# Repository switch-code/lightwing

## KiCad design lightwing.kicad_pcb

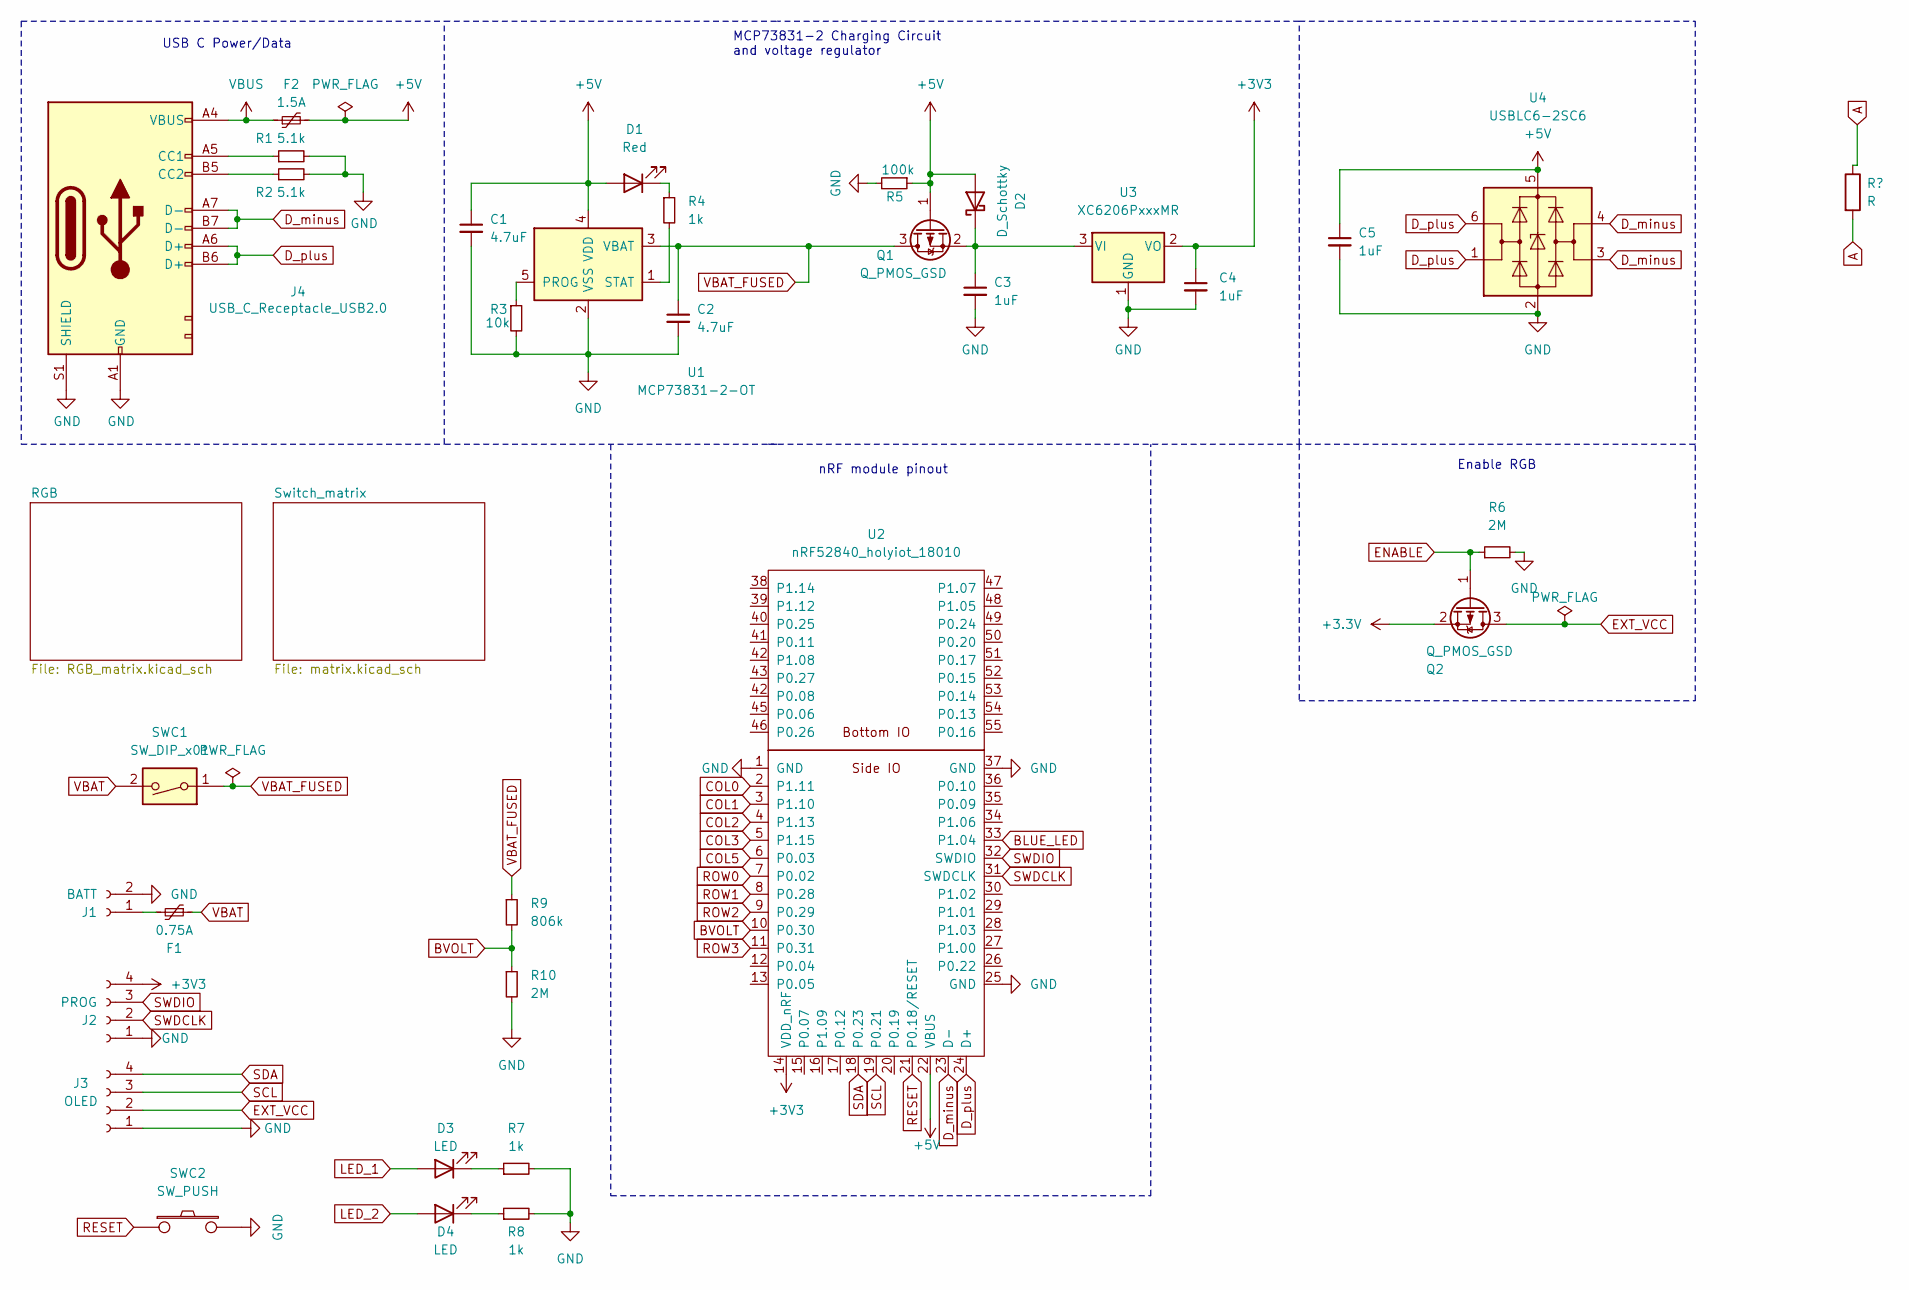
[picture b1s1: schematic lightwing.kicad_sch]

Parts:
C1, C2: 4.7uF; C-0805_2012Metric
C3, C4, C5: 1uF; C-0805_2012Metric
D1: Red; LED_0603_1608Metric_Castellated
D2: D_Schottky; D_1206_3216Metric
D3, D4: LED; LED_0603_1608Metric_Castellated
F1: 0.75A; Fuse_1206_3216Metric
F2: 1.5A; Fuse_1206_3216Metric
J1: BATT; JST_EH_B2B-EH-A_1x02_P2.50mm_Vertical
J2: PROG; PinHeader_1x04_P2.54mm_Vertical
J3: OLED; SSD1306-0.91-OLED-4pin-128x32
J4: USB_C_Receptacle_USB2.0; HRO-TYPE-C-31-M-12-HandSoldering-NoSBU
Q1, Q2: Q_PMOS_GSD; SOT-23
R1, R2: 5.1k; R-0805_2012Metric
R3: 10k; R-0805_2012Metric
R4, R7, R8: 1k; R-0805_2012Metric
R5: 100k; R-0805_2012Metric
R6, R10: 2M; R-0805_2012Metric
R9: 806k; R-0805_2012Metric
SWC1: SW_DIP_x01; SW_DIP_SPSTx01_Slide_6.7x4.1mm_W6.73mm_P2.54mm_LowProfile_J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
SWC2: SW_PUSH; SW_Push_1P1T_NO_6x6mm_H9.5mm
U1: MCP73831-2-OT; SOT-23-5
U2: nRF52840_holyiot_18010; nRF52840_holyiot_18010_HS_simple
U3: XC6206PxxxMR; SOT-23
U4: USBLC6-2SC6; SOT-23-6

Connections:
+5V: C1.1, C5.1, D1.2 (A), D2.2 (A), F2.2, Q1.1 (G), R5.1, U1.4 (VDD), U2.22 (VBUS), U4.5 (VBUS)
BLUE_LED: U2.33 (P1.04)
BVOLT: R9.2, R10.1, U2.10 (P0.30)
COL0: U2.2 (P1.11); also elsewhere on the board
COL1: U2.3 (P1.10); also elsewhere on the board
COL2: U2.4 (P1.13); also elsewhere on the board
COL3: U2.5 (P1.15); also elsewhere on the board
COL5: U2.6 (P0.03)
ENABLE: Q2.1 (G), R6.1
EXT_VCC: J3.2, Q2.3 (D); also elsewhere on the board
GND: C1.2, C2.2, C3.2, C4.2, C5.2, J1.2, J2.1, J3.1, J4.A1 (GND), J4.B1 (GND), J4.S1 (SHIELD), R1.2, R2.2, R3.2, R5.2, R6.2, R7.2, R8.2, R10.2, SWC2.2, U1.2 (VSS), U2.1 (GND), U2.25 (GND), U2.37 (GND), U3.1 (GND), U4.2 (GND); also elsewhere on the board
LED_1: D3.2 (A)
LED_2: D4.2 (A)
unnamed: C3.1, D2.1 (K), Q1.2 (S), U3.3 (VI)
unnamed: D1.1 (K), R4.1
unnamed: D3.1 (K), R7.1
unnamed: D4.1 (K), R8.1
unnamed: F1.2, J1.1
unnamed: J4.A5 (CC1), R1.1
unnamed: J4.B5 (CC2), R2.1
unnamed: R3.1, U1.5 (PROG)
unnamed: R4.2, U1.1 (STAT)
RESET: SWC2.1, U2.21 (P0.18/RESET)
ROW0: U2.7 (P0.02); also elsewhere on the board
ROW1: U2.8 (P0.28); also elsewhere on the board
ROW2: U2.9 (P0.29); also elsewhere on the board
ROW3: U2.11 (P0.31); also elsewhere on the board
SCL: J3.3, U2.19 (P0.21)
SDA: J3.4, U2.18 (P0.23)
SWDCLK: J2.2, U2.31 (SWDCLK)
SWDIO: J2.3, U2.32 (SWDIO)
VBAT: F1.1, SWC1.2
VBAT_FUSED: C2.1, Q1.3 (D), R9.1, SWC1.1, U1.3 (VBAT)
VBUS: F2.1, J4.A4 (VBUS), J4.B4 (VBUS)

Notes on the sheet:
Enable RGB
MCP73831-2 Charging Circuit and voltage regulator
USB C Power/Data
nRF module pinout

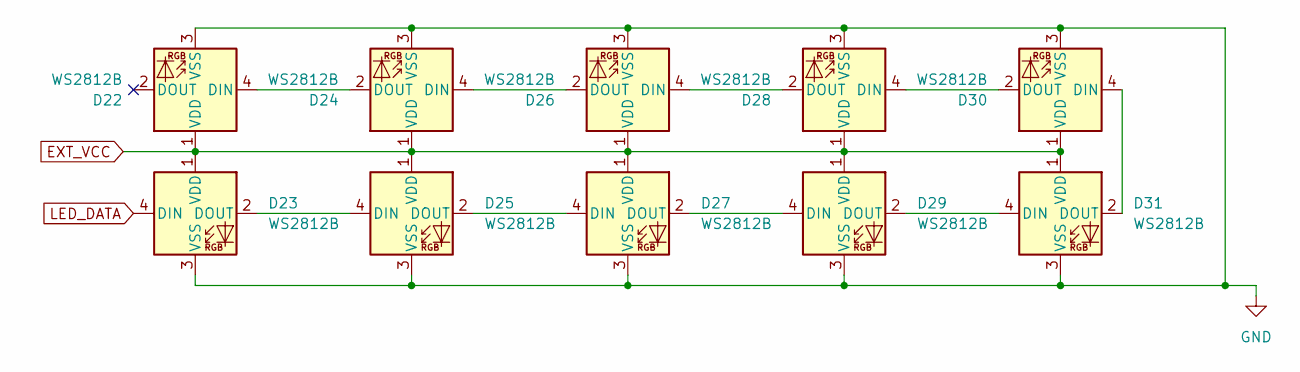
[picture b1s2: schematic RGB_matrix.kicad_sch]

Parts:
D22, D23, D24, D25, D26, D27, D28, D29, D30, D31: WS2812B; SK6812Mini-E

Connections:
EXT_VCC: D22.1 (VDD), D23.1 (VDD), D24.1 (VDD), D25.1 (VDD), D26.1 (VDD), D27.1 (VDD), D28.1 (VDD), D29.1 (VDD), D30.1 (VDD), D31.1 (VDD); also elsewhere on the board
GND: D22.3 (VSS), D23.3 (VSS), D24.3 (VSS), D25.3 (VSS), D26.3 (VSS), D27.3 (VSS), D28.3 (VSS), D29.3 (VSS), D30.3 (VSS), D31.3 (VSS); also elsewhere on the board
LED_DATA: D23.4 (DIN)
unnamed: D22.4 (DIN), D24.2 (DOUT)
unnamed: D23.2 (DOUT), D25.4 (DIN)
unnamed: D24.4 (DIN), D26.2 (DOUT)
unnamed: D25.2 (DOUT), D27.4 (DIN)
unnamed: D26.4 (DIN), D28.2 (DOUT)
unnamed: D27.2 (DOUT), D29.4 (DIN)
unnamed: D28.4 (DIN), D30.2 (DOUT)
unnamed: D29.2 (DOUT), D31.4 (DIN)
unnamed: D30.4 (DIN), D31.2 (DOUT)

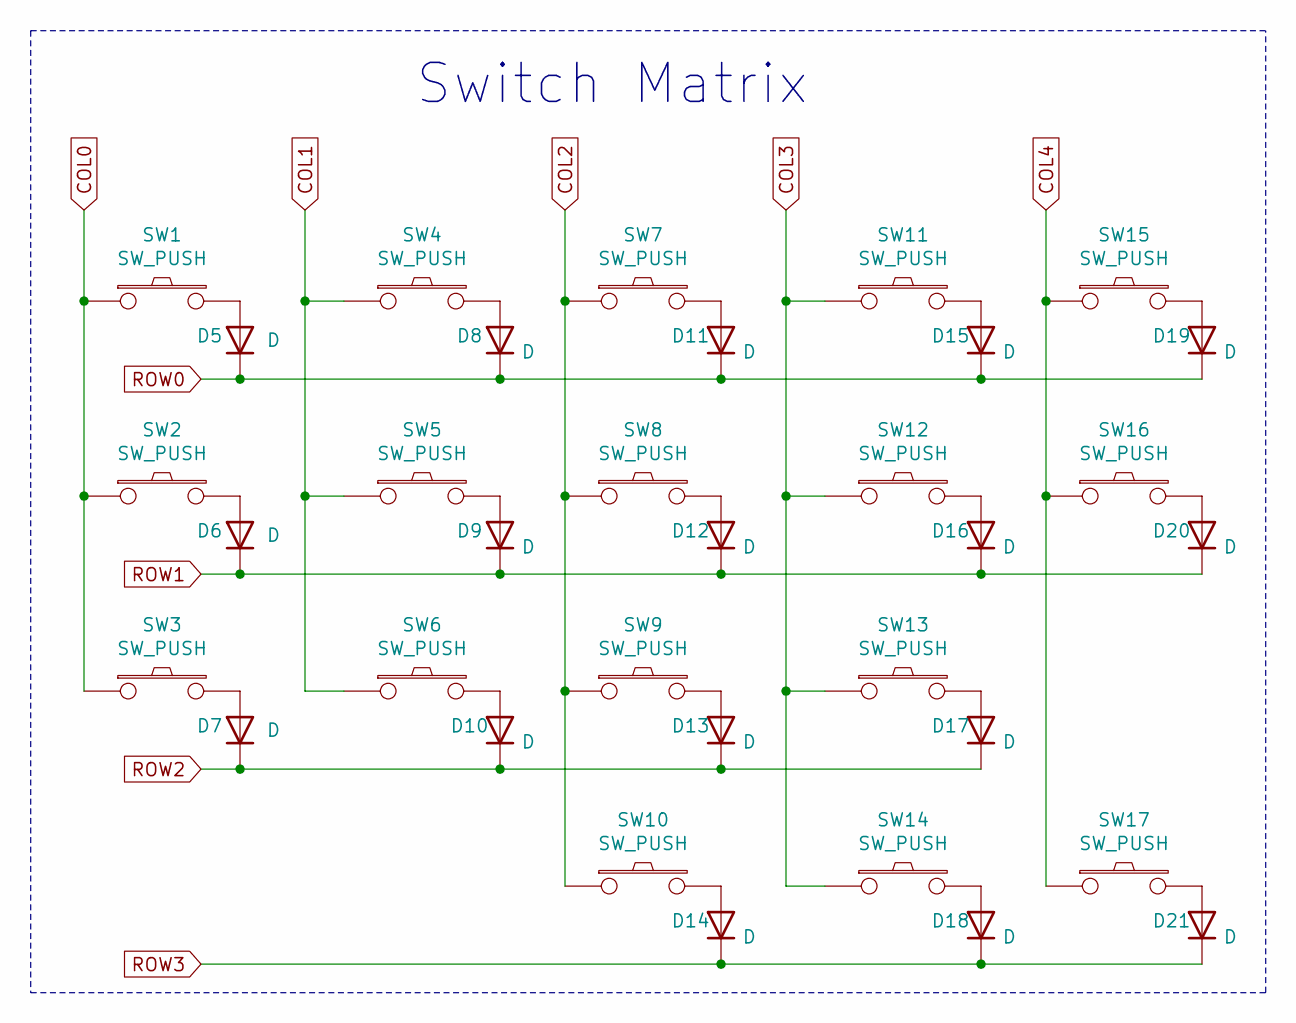
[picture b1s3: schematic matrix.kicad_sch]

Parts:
D5, D6, D7, D8, D9, D10, D11, D12, D13, D14, D15, D16, D17, D18, D19, D20, D21: D; D_SOD-123_smaller
SW1, SW2, SW3, SW4, SW5, SW6, SW7, SW8, SW9, SW11, SW12, SW13, SW15, SW16: SW_PUSH; Kailh_socket_PG1350_reversible
SW10, SW14, SW17: SW_PUSH; Kailh_socket_PG1350_reversible_1.5U

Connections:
COL0: SW1.1, SW2.1, SW3.1; also elsewhere on the board
COL1: SW4.1, SW5.1, SW6.1; also elsewhere on the board
COL2: SW7.1, SW8.1, SW9.1, SW10.1; also elsewhere on the board
COL3: SW11.1, SW12.1, SW13.1, SW14.1; also elsewhere on the board
COL4: SW15.1, SW16.1, SW17.1
unnamed: D5.2 (A), SW1.2
unnamed: D6.2 (A), SW2.2
unnamed: D7.2 (A), SW3.2
unnamed: D8.2 (A), SW4.2
unnamed: D9.2 (A), SW5.2
unnamed: D10.2 (A), SW6.2
unnamed: D11.2 (A), SW7.2
unnamed: D12.2 (A), SW8.2
unnamed: D13.2 (A), SW9.2
unnamed: D14.2 (A), SW10.2
unnamed: D15.2 (A), SW11.2
unnamed: D16.2 (A), SW12.2
unnamed: D17.2 (A), SW13.2
unnamed: D18.2 (A), SW14.2
unnamed: D19.2 (A), SW15.2
unnamed: D20.2 (A), SW16.2
unnamed: D21.2 (A), SW17.2
ROW0: D5.1 (K), D8.1 (K), D11.1 (K), D15.1 (K), D19.1 (K); also elsewhere on the board
ROW1: D6.1 (K), D9.1 (K), D12.1 (K), D16.1 (K), D20.1 (K); also elsewhere on the board
ROW2: D7.1 (K), D10.1 (K), D13.1 (K), D17.1 (K); also elsewhere on the board
ROW3: D14.1 (K), D18.1 (K), D21.1 (K); also elsewhere on the board

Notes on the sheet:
Switch Matrix

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
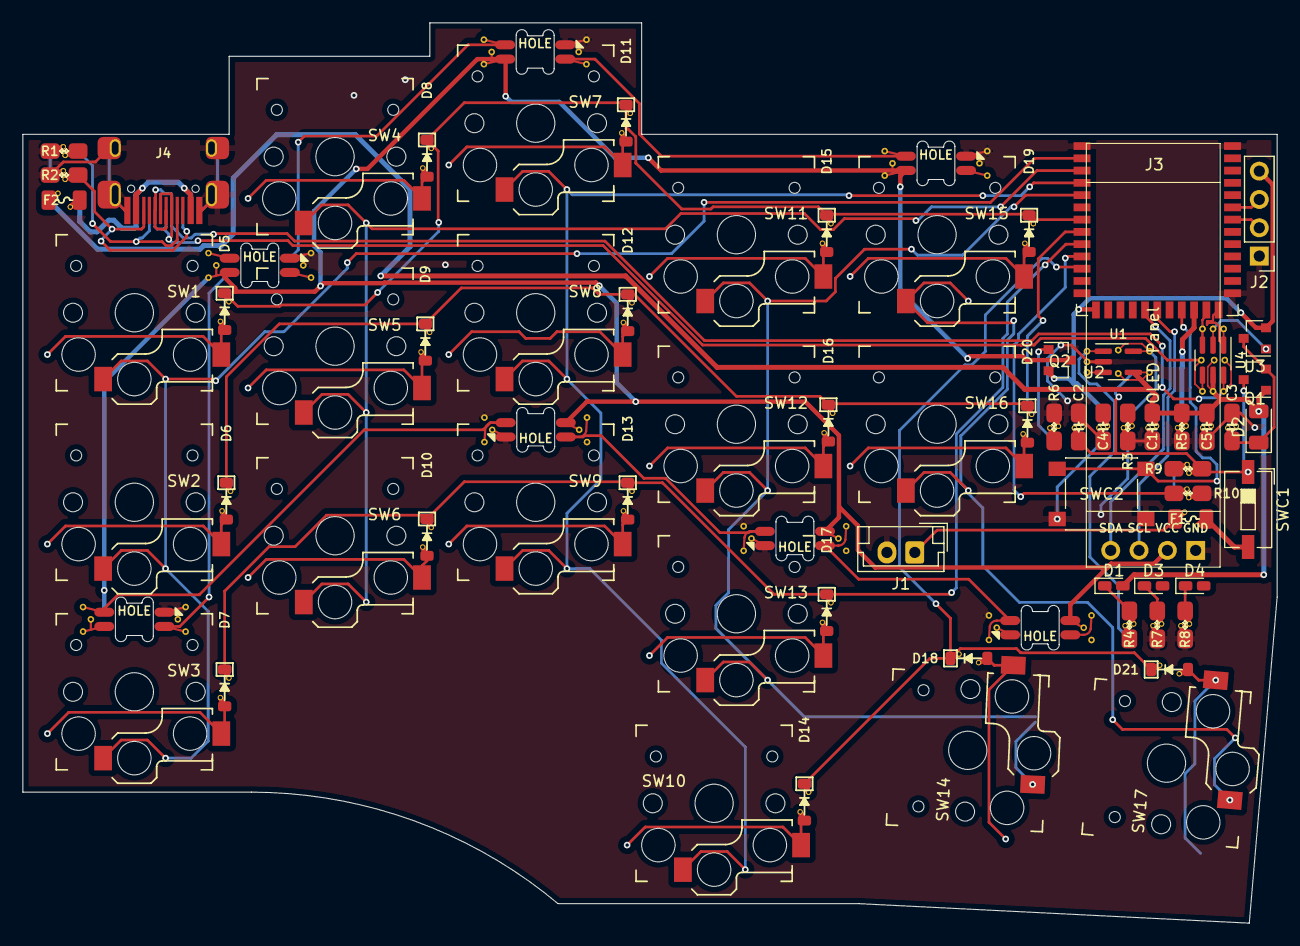
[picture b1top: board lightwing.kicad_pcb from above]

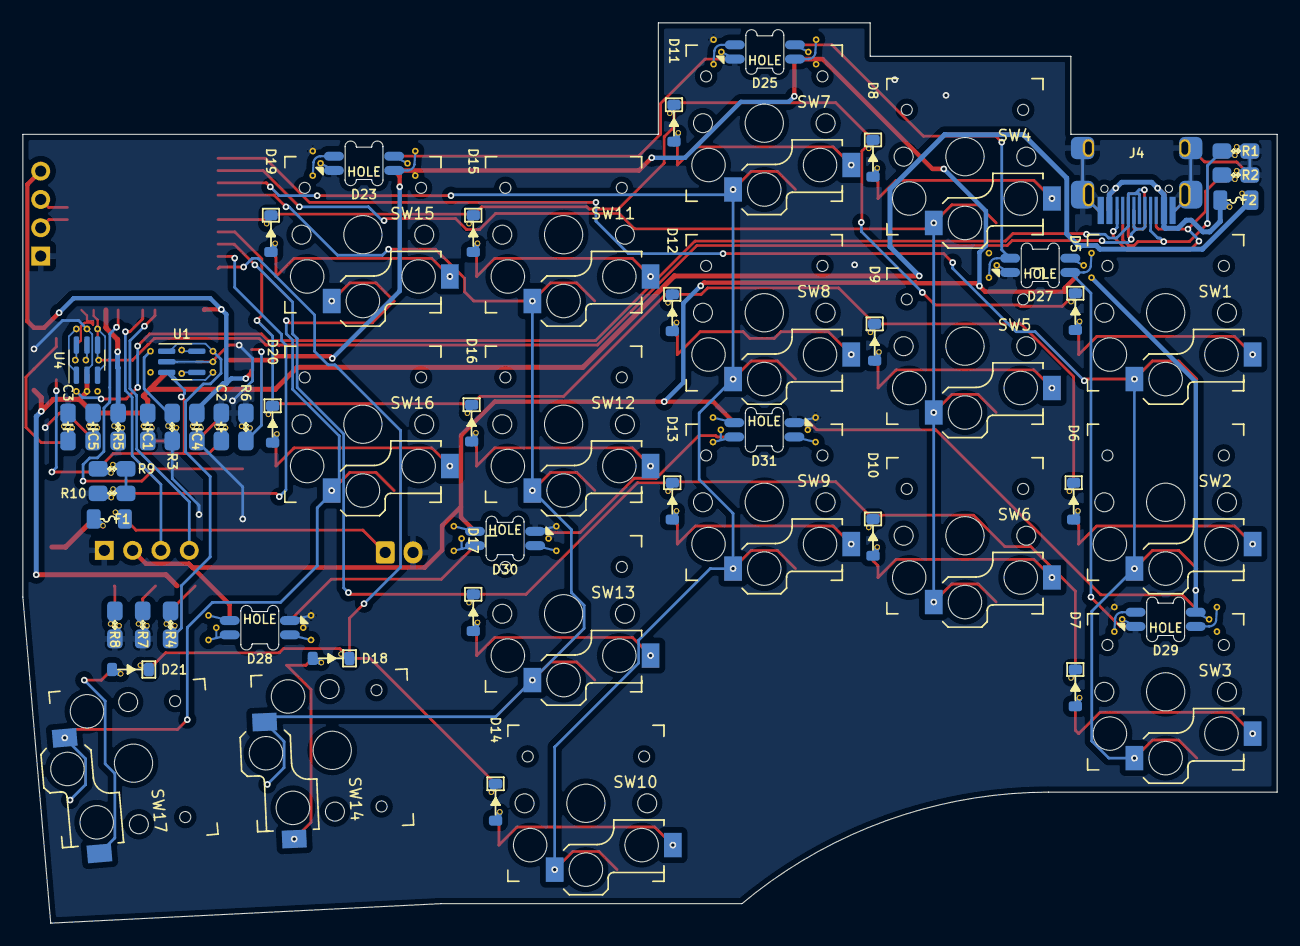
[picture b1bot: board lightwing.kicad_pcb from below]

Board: 2 copper layers, 112.5 x 80.8 mm, 74 parts (5 on the bottom side), 59 nets.

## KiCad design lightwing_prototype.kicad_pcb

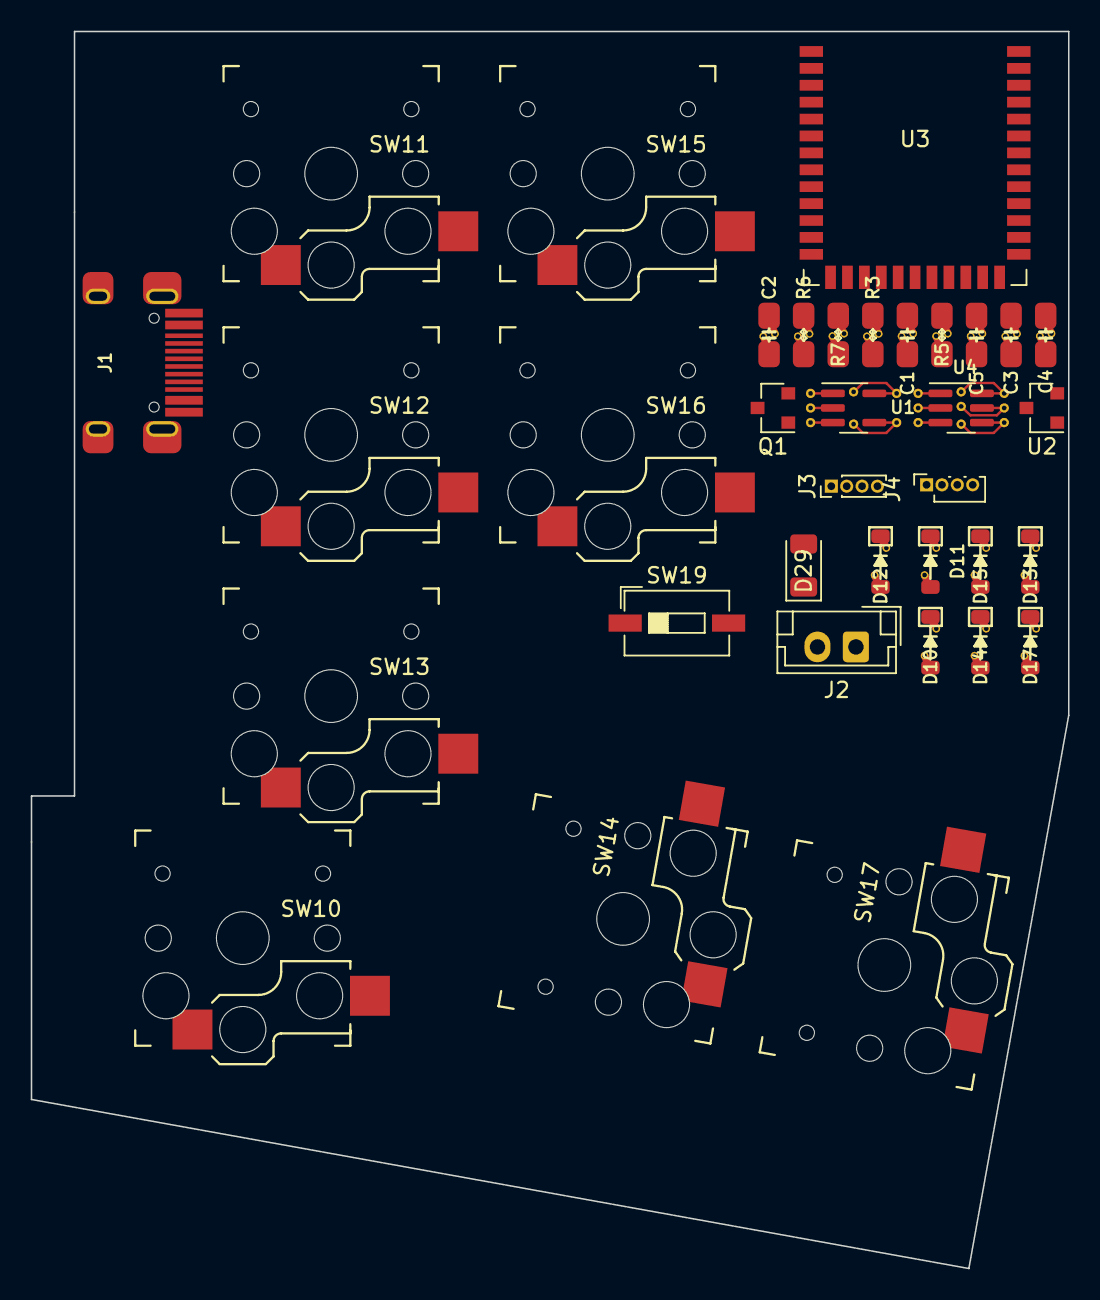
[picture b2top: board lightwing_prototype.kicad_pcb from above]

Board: 2 copper layers, 67.5 x 80.5 mm, 35 parts (0 on the bottom side), 30 nets, no tracks yet.

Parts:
C1, C2: 4.7uF; C-0805_2012Metric
C3, C4, C5: 1uF; C-0805_2012Metric
D10, D11, D12, D13, D14, D15, D17: D; D_SOD-123_smaller
D29: D_Schottky; D_1206_3216Metric
J1: USB_C_Receptacle_USB2.0; HRO-TYPE-C-31-M-12-HandSoldering-NoSBU
J2: BATT; JST_EH_B2B-EH-A_1x02_P2.50mm_Vertical
J3: OLED; PinHeader_1x04_P1.00mm_Vertical
J4: PROG; PinSocket_1x04_P1.00mm_Vertical
Q1: Q_PMOS_GSD; SOT-23
R3: 2k; R-0805_2012Metric
R5: 100k; R-0805_2012Metric
R6: 806k; R-0805_2012Metric
R7: 2M; R-0805_2012Metric
SW10: SW_PUSH; Kailh_socket_PG1350_reversible_1.5U
SW11, SW12, SW13, SW15, SW16: SW_PUSH; Kailh_socket_PG1350_reversible
SW14, SW17: SW_PUSH; Kailh_socket_PG1350_reversible_2U
SW19: SW_DIP_x01; SW_DIP_SPSTx01_Slide_6.7x4.1mm_W6.73mm_P2.54mm_LowProfile_J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
U1: MCP73831-2-OT; SOT-23-5
U2: XC6206PxxxMR; SOT-23
U3: nRF52840_holyiot_18010; nRF52840_holyiot_18010_HS_simple
U4: USBLC6-2SC6; SOT-23-6

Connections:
+3V3: C4.1, J4.4, U2.2 (VO), U3.14 (VDD_nRF)
BVOLT: R6.2, R7.1, U3.10 (P0.30)
COL2: SW10.1, U3.28 (P1.03)
COL3: SW11.1, SW12.1, SW13.1, SW14.1, U3.27 (P1.00)
COL4: SW15.1, SW16.1, SW17.1
D+: U3.24 (D+), U4.3 (I/O2)
D-: U3.23 (D-), U4.1 (I/O1)
D_minus: J1.A7 (D-), J1.B7 (D-), U4.6 (I/O1)
D_plus: J1.A6 (D+), J1.B6 (D+), U4.4 (I/O2)
GND: C1.2, C2.2, C3.2, C4.2, C5.2, J1.A1 (GND), J1.B1 (GND), J1.S1 (SHIELD), J2.2, J3.1, J4.1, R3.2, R5.2, R7.2, U1.2 (VSS), U2.1 (GND), U3.1 (GND), U3.25 (GND), U3.37 (GND), U4.2 (GND)
unnamed: C3.1, D29.1 (K), Q1.2 (S), U2.3 (VI)
unnamed: D10.2 (A), SW10.2
unnamed: D11.2 (A), SW11.2
unnamed: D12.2 (A), SW12.2
unnamed: D13.2 (A), SW13.2
unnamed: D14.2 (A), SW14.2
unnamed: D15.2 (A), SW15.2
unnamed: D17.2 (A), SW17.2
unnamed: R3.1, U1.5 (PROG)
ROW0: D11.1 (K), D15.1 (K), U3.9 (P0.29)
ROW1: D12.1 (K), U3.8 (P0.28)
ROW2: D13.1 (K), U3.7 (P0.02)
ROW3: D10.1 (K), D14.1 (K), D17.1 (K), U3.6 (P0.03)
SCL: J3.3, U3.19 (P0.21)
SDA: J3.4, U3.18 (P0.23)
SWDCLK: J4.2, U3.31 (SWDCLK)
SWDIO: J4.3, U3.32 (SWDIO)
VBAT: C2.1, Q1.3 (D), R6.1, SW19.1, U1.3 (VBAT)
VBAT_IN: J2.1, SW19.2
VBUS: C1.1, C5.1, D29.2 (A), J1.A4 (VBUS), J1.B4 (VBUS), Q1.1 (G), R5.1, U1.4 (VDD), U3.22 (VBUS), U4.5 (VBUS)
